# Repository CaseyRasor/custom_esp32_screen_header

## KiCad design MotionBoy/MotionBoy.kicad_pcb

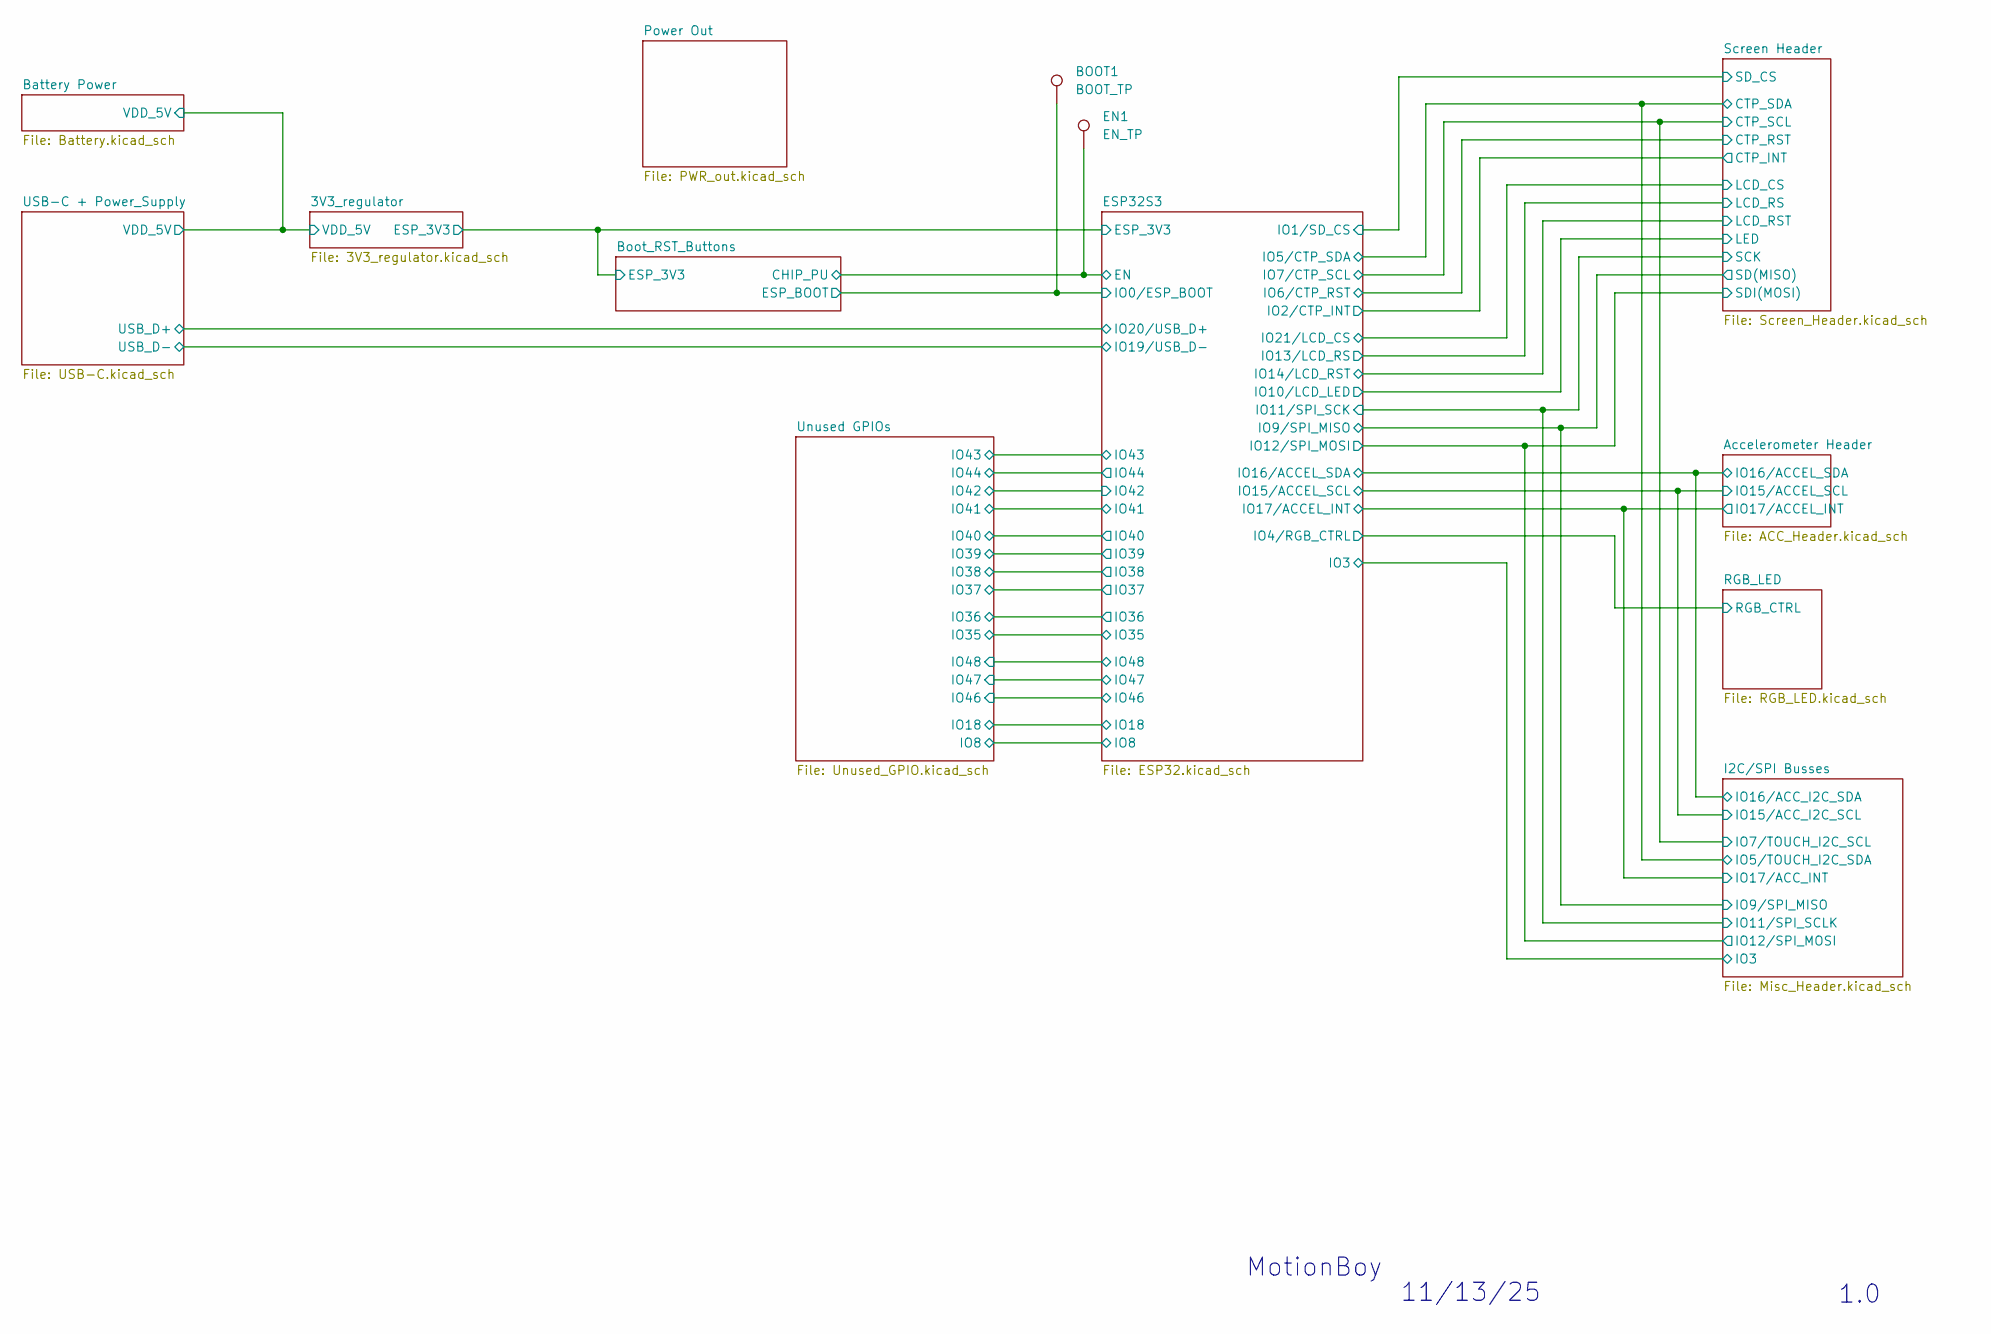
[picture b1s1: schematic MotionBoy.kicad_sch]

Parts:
BOOT1: BOOT_TP; TestPoint_Keystone_5010-5014_Multipurpose
EN1: EN_TP; TestPoint_Keystone_5010-5014_Multipurpose

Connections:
/Boot_RST_Buttons/CHIP_PU: EN1.1; also elsewhere on the board
/Boot_RST_Buttons/ESP_BOOT: BOOT1.1; also elsewhere on the board

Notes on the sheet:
MotionBoy
1.0
11/13/25

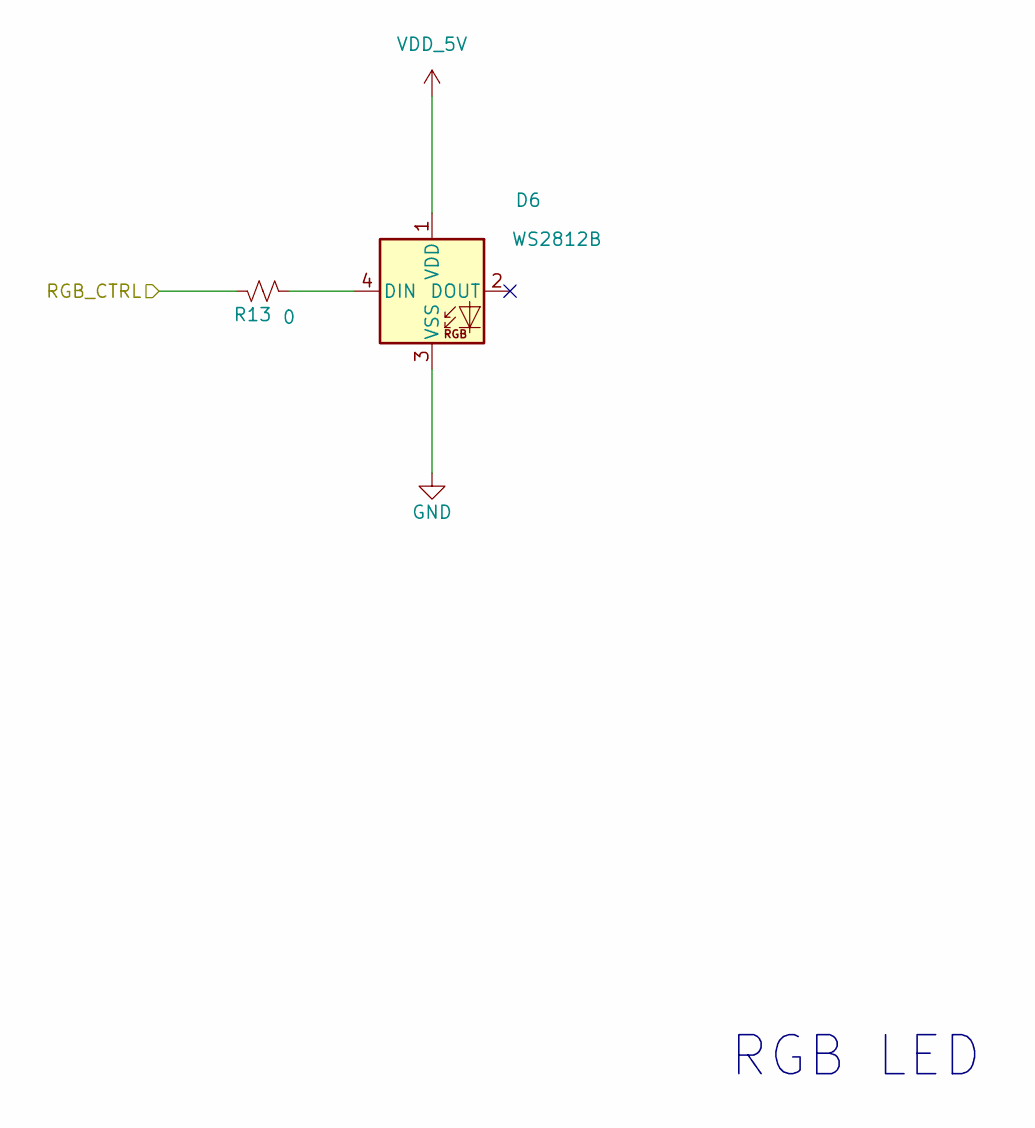
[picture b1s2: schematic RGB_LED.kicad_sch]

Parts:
D6: WS2812B; LED_WS2812B_PLCC4_5.0x5.0mm_P3.2mm
R13: 0; R_0805_2012Metric

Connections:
/ESP32S3/IO4/RGB_CTRL: R13.2; also elsewhere on the board
GND: D6.3 (VSS); also elsewhere on the board
unnamed: D6.4 (DIN), R13.1
VDD_5V: D6.1 (VDD); also elsewhere on the board

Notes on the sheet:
RGB LED

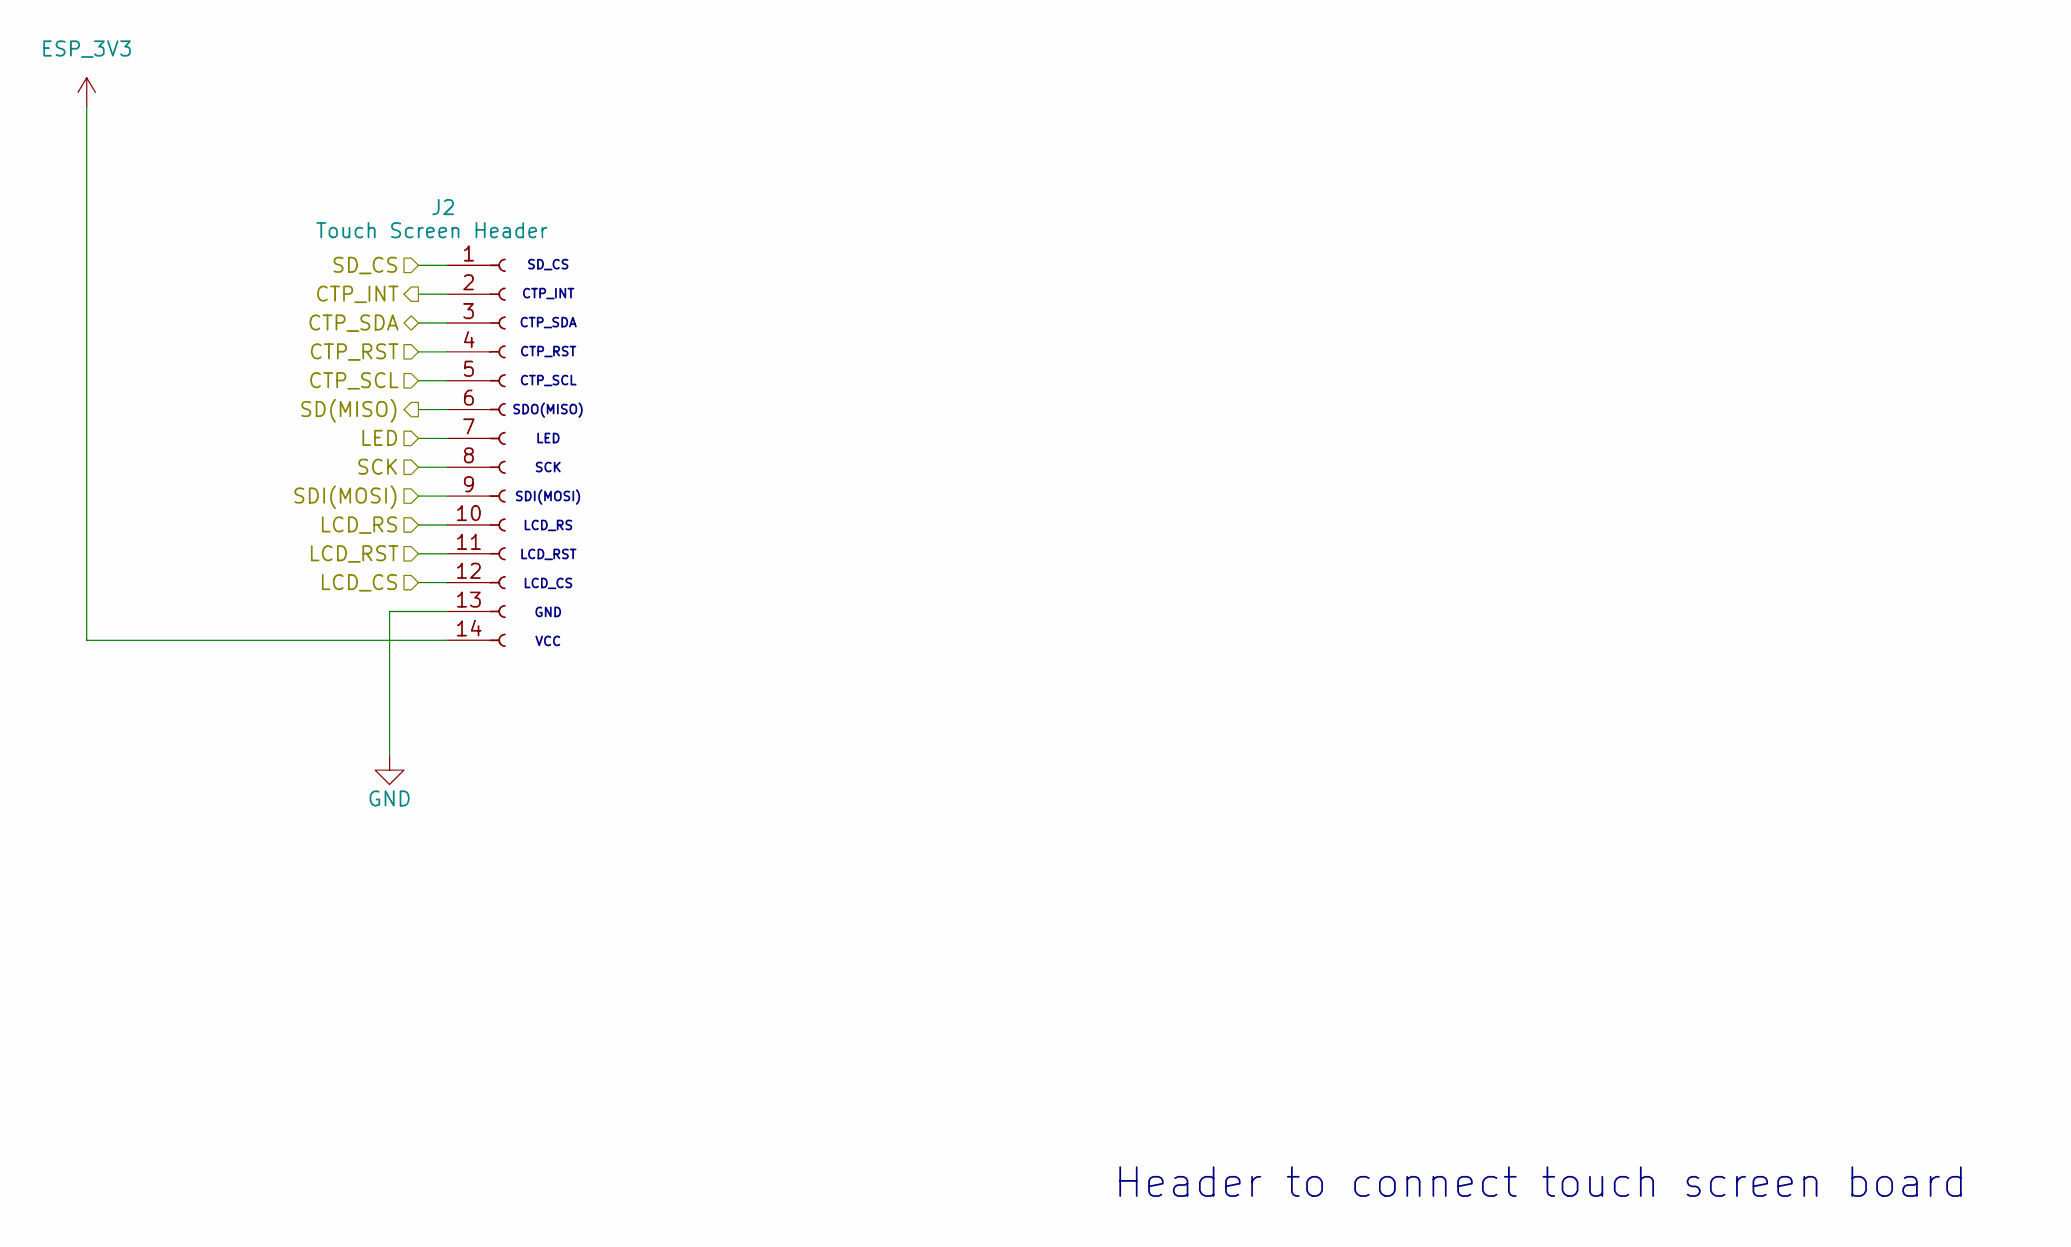
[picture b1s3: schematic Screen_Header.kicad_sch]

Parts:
J2: Touch Screen Header; PinSocket_1x14_P2.54mm_Vertical

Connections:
/ESP32S3/IO1/SD_CS: J2.1; also elsewhere on the board
/ESP32S3/IO2/CTP_INT: J2.2; also elsewhere on the board
/ESP32S3/IO5/CTP_SDA: J2.3; also elsewhere on the board
/ESP32S3/IO6/CTP_RST: J2.4; also elsewhere on the board
/ESP32S3/IO7/CTP_SCL: J2.5; also elsewhere on the board
/ESP32S3/IO9/SPI_MISO: J2.6; also elsewhere on the board
/ESP32S3/IO10/LCD_LED: J2.7; also elsewhere on the board
/ESP32S3/IO11/SPI_SCK: J2.8; also elsewhere on the board
/ESP32S3/IO12/SPI_MOSI: J2.9; also elsewhere on the board
/ESP32S3/IO13/LCD_RS: J2.10; also elsewhere on the board
/ESP32S3/IO14/LCD_RST: J2.11; also elsewhere on the board
/ESP32S3/IO21/LCD_CS: J2.12; also elsewhere on the board
ESP_3V3: J2.14; also elsewhere on the board
GND: J2.13; also elsewhere on the board

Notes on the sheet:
Header to connect touch screen board
SD_CS CTP_INT CTP_SDA CTP_RST CTP_SCL SDO(MISO) LED SCK SDI(MOSI) LCD_RS LCD_RST LCD_CS GND VCC

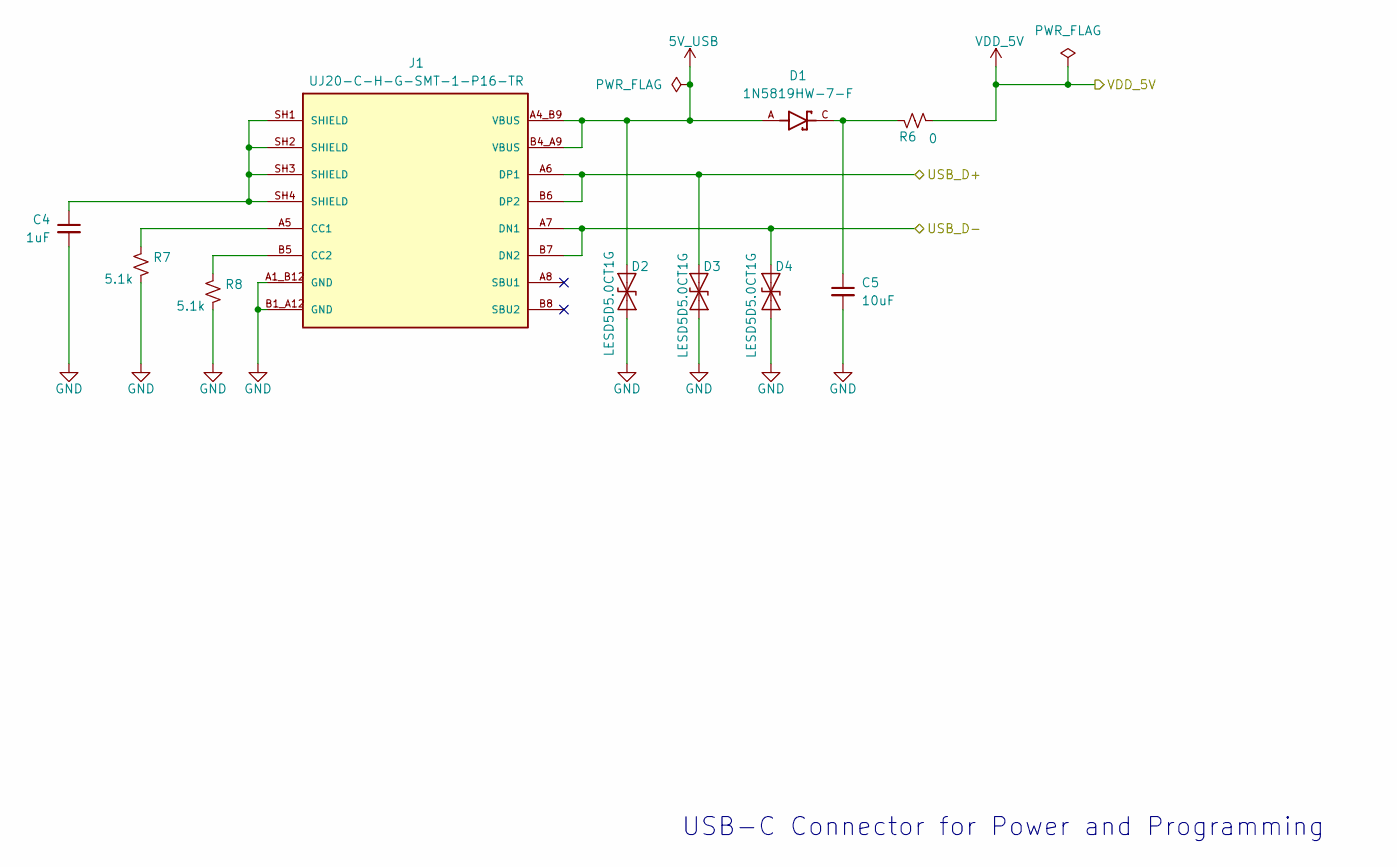
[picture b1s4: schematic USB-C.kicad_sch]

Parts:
C4: 1uF; C_0805_2012Metric
C5: 10uF; C_0805_2012Metric
D1: 1N5819HW-7-F; SOD3715X145N; PARTREV 18-2
D2, D3, D4: LESD5D5.0CT1G; D_SOD-323
J1: UJ20-C-H-G-SMT-1-P16-TR; SAMESKY_UJ20-C-H-G-SMT-1-P16-TR; PARTREV 1.0
R6: 0; R_0805_2012Metric
R7, R8: 5.1k; R_0805_2012Metric

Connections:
5V_USB: D1.A, D2.2 (A2), J1.A4_B9 (VBUS), J1.B4_A9 (VBUS); also elsewhere on the board
/ESP32S3/IO19/USB_D-: D4.2 (A2), J1.A7 (DN1), J1.B7 (DN2); also elsewhere on the board
/ESP32S3/IO20/USB_D+: D3.2 (A2), J1.A6 (DP1), J1.B6 (DP2); also elsewhere on the board
GND: C4.2, C5.2, D2.1 (A1), D3.1 (A1), D4.1 (A1), J1.A1_B12 (GND), J1.B1_A12 (GND), R7.2, R8.2; also elsewhere on the board
unnamed: C4.1, J1.SH1 (SHIELD), J1.SH2 (SHIELD), J1.SH3 (SHIELD), J1.SH4 (SHIELD)
unnamed: C5.1, D1.C, R6.2
unnamed: J1.A5 (CC1), R7.1
unnamed: J1.B5 (CC2), R8.1
VDD_5V: R6.1; also elsewhere on the board

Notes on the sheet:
USB-C Connector for Power and Programming

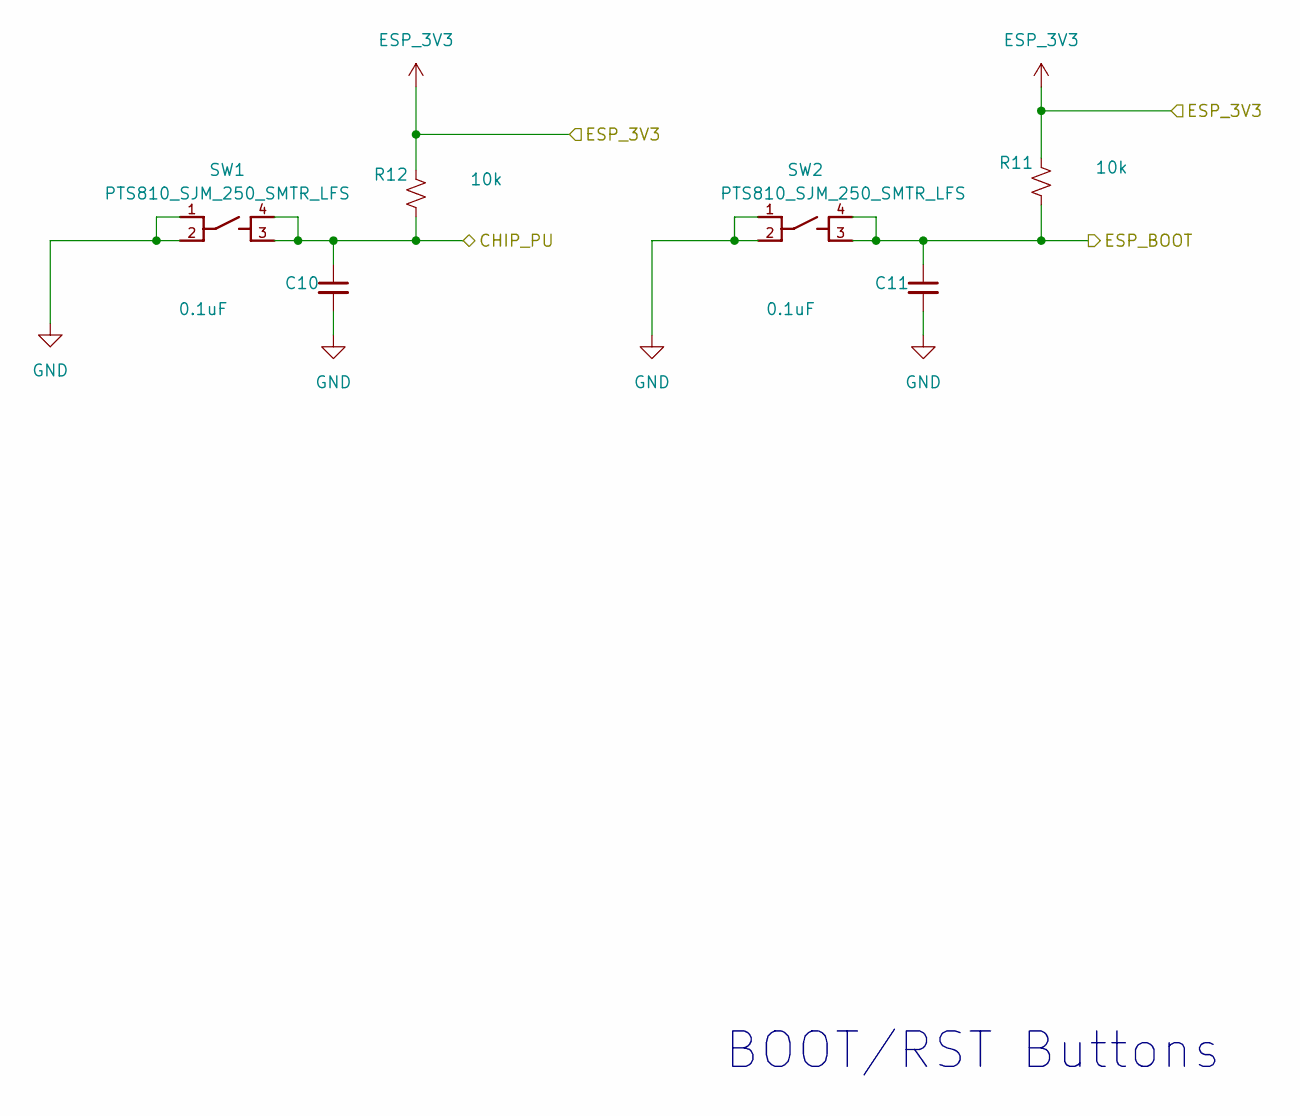
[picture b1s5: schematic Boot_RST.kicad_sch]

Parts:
C10, C11: 0.1uF; C_0805_2012Metric
R11, R12: 10k; R_0805_2012Metric
SW1, SW2: PTS810_SJM_250_SMTR_LFS; SW_PTS810_SJM_250_SMTR_LFS

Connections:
/Boot_RST_Buttons/CHIP_PU: C10.1, R12.1, SW1.3, SW1.4; also elsewhere on the board
/Boot_RST_Buttons/ESP_BOOT: C11.1, R11.1, SW2.3, SW2.4; also elsewhere on the board
ESP_3V3: R11.2, R12.2; also elsewhere on the board
GND: C10.2, C11.2, SW1.1, SW1.2, SW2.1, SW2.2; also elsewhere on the board

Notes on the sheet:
BOOT/RST Buttons

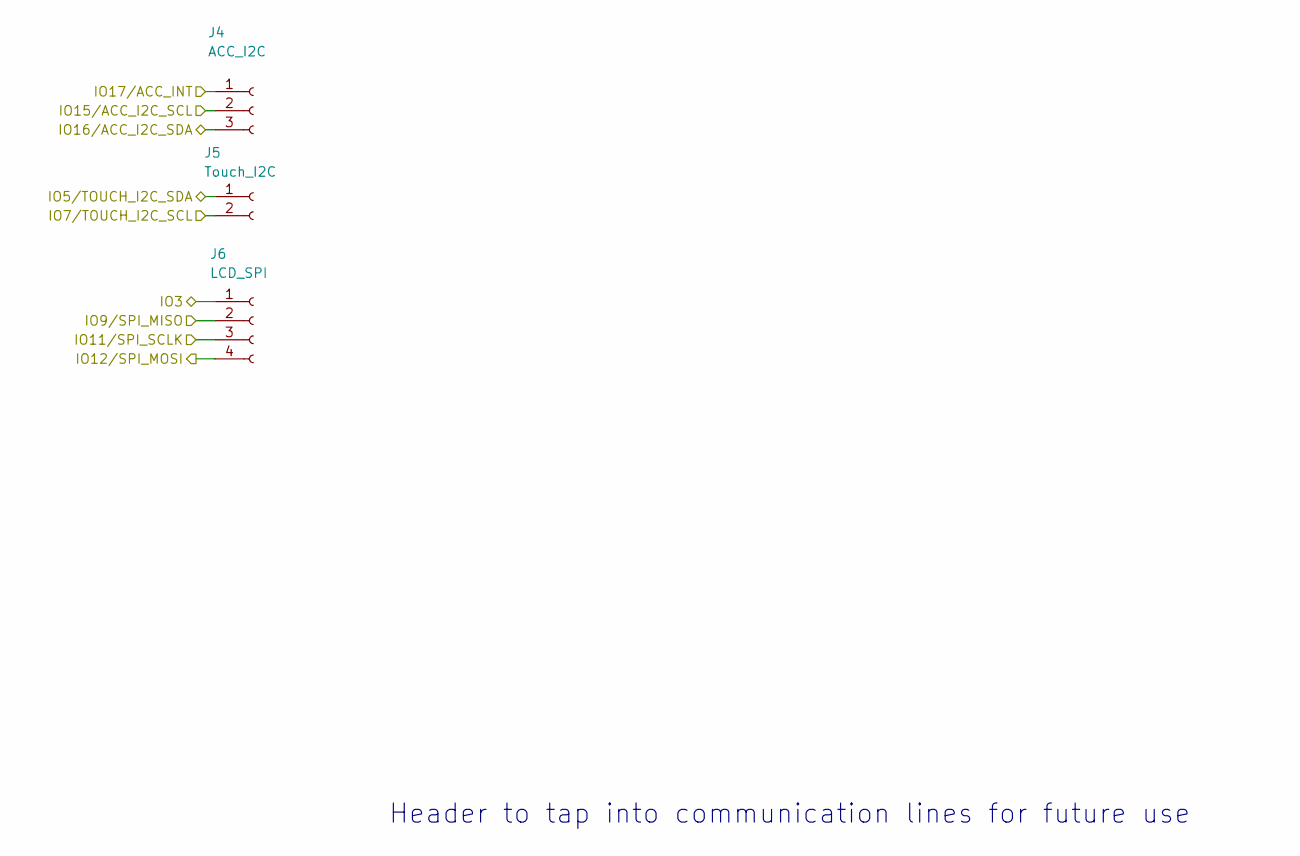
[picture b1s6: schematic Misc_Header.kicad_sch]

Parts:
J4: ACC_I2C; JST_PH_S3B-PH-K_1x03_P2.00mm_Horizontal
J5: Touch_I2C; JST_PH_S2B-PH-K_1x02_P2.00mm_Horizontal
J6: LCD_SPI; JST_PH_S4B-PH-K_1x04_P2.00mm_Horizontal

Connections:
/Accelerometer Header/IO15/ACCEL_SCL: J4.2; also elsewhere on the board
/Accelerometer Header/IO16/ACCEL_SDA: J4.3; also elsewhere on the board
/Accelerometer Header/IO17/ACCEL_INT: J4.1; also elsewhere on the board
/ESP32S3/IO3: J6.1; also elsewhere on the board
/ESP32S3/IO5/CTP_SDA: J5.1; also elsewhere on the board
/ESP32S3/IO7/CTP_SCL: J5.2; also elsewhere on the board
/ESP32S3/IO9/SPI_MISO: J6.2; also elsewhere on the board
/ESP32S3/IO11/SPI_SCK: J6.3; also elsewhere on the board
/ESP32S3/IO12/SPI_MOSI: J6.4; also elsewhere on the board

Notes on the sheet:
Header to tap into communication lines for future use

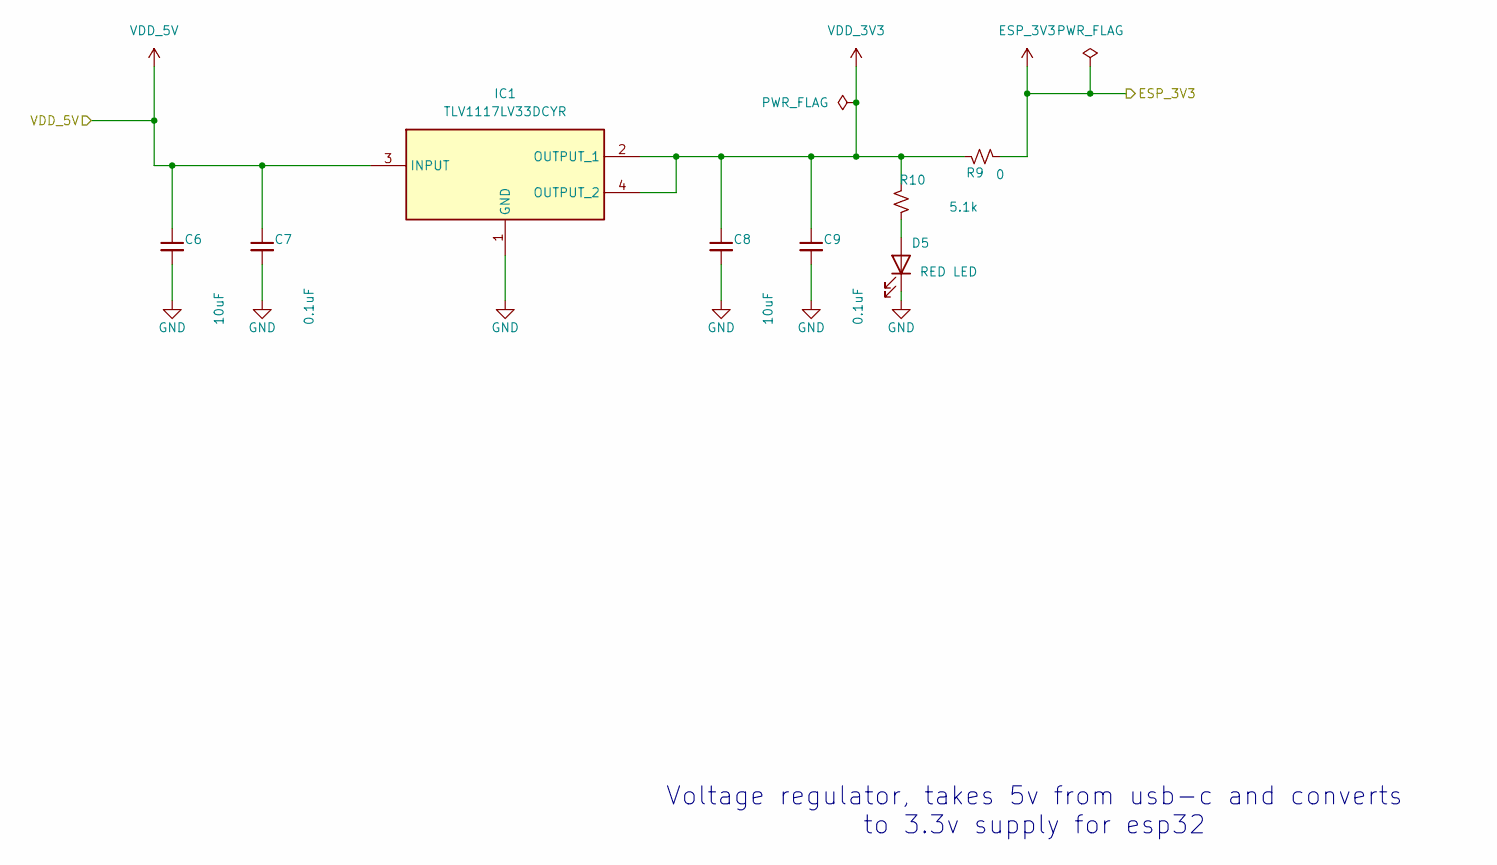
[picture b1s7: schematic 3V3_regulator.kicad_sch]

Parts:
C6, C8: 10uF; C_0805_2012Metric
C7, C9: 0.1uF; C_0805_2012Metric
D5: RED LED; LED_0805_2012Metric
IC1: TLV1117LV33DCYR; SOT230P700X180-4N; Mouser Part Number 595-TLV1117LV33DCYR
R9: 0; R_0805_2012Metric
R10: 5.1k; R_0805_2012Metric

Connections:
ESP_3V3: R9.1; also elsewhere on the board
GND: C6.2, C7.2, C8.2, C9.2, D5.1 (K), IC1.1 (GND); also elsewhere on the board
unnamed: D5.2 (A), R10.2
VDD_3V3: C8.1, C9.1, IC1.2 (OUTPUT_1), IC1.4 (OUTPUT_2), R9.2, R10.1; also elsewhere on the board
VDD_5V: C6.1, C7.1, IC1.3 (INPUT); also elsewhere on the board

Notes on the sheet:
Voltage regulator, takes 5v from usb-c and converts to 3.3v supply for esp32

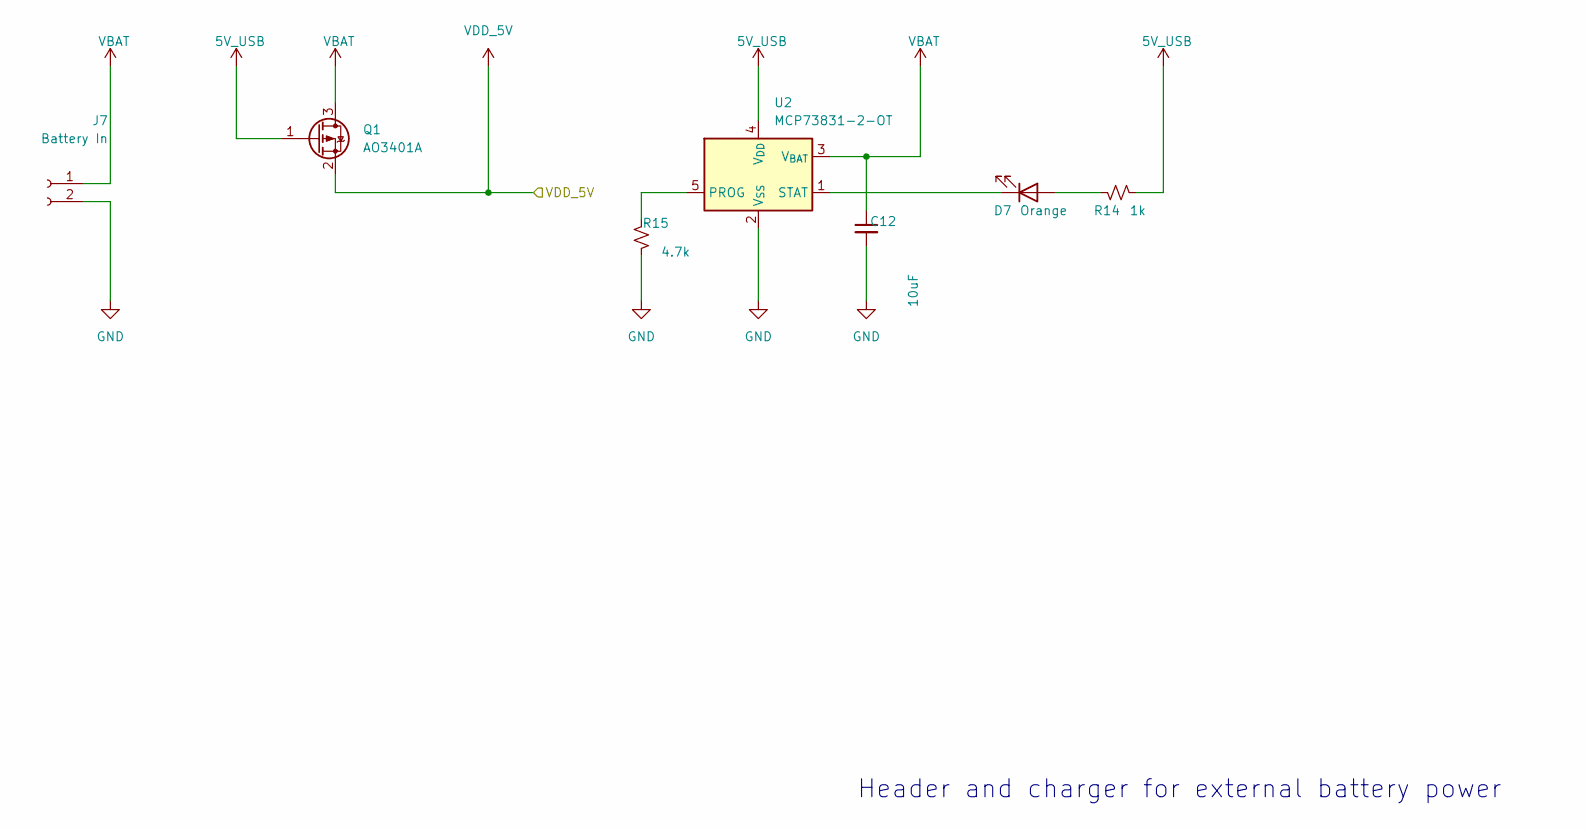
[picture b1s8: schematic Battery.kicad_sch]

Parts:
C12: 10uF; C_0805_2012Metric
D7: Orange; LED_0805_2012Metric
J7: Battery In; JST_PH_S2B-PH-K_1x02_P2.00mm_Horizontal
Q1: AO3401A; SOT-23
R14: 1k; R_0805_2012Metric
R15: 4.7k; R_0805_2012Metric
U2: MCP73831-2-OT; SOT-23-5

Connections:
5V_USB: Q1.1 (G), R14.1, U2.4 (V_{DD}); also elsewhere on the board
GND: C12.2, J7.2, R15.2, U2.2 (V_{SS}); also elsewhere on the board
unnamed: D7.2 (A), R14.2
unnamed: D7.1 (K), U2.1 (STAT)
unnamed: R15.1, U2.5 (PROG)
VBAT: C12.1, J7.1, Q1.3 (D), U2.3 (V_{BAT})
VDD_5V: Q1.2 (S); also elsewhere on the board

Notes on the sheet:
Header and charger for external battery power

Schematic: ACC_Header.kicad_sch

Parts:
J3: Accelerometer Header; PinSocket_1x08_P2.54mm_Vertical

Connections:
/Accelerometer Header/IO15/ACCEL_SCL: J3.3; also elsewhere on the board
/Accelerometer Header/IO16/ACCEL_SDA: J3.4; also elsewhere on the board
/Accelerometer Header/IO17/ACCEL_INT: J3.8; also elsewhere on the board
ESP_3V3: J3.1; also elsewhere on the board
GND: J3.2, J3.7; also elsewhere on the board

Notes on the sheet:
Header to connect accelerometer board
VCC GND SCL SDA XDA XCL ADO INT

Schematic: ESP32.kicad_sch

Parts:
C1: 10uF; C_0805_2012Metric
C2, C3: 0.1uF; C_0805_2012Metric
GND1: GND_TP; TestPoint_Keystone_5010-5014_Multipurpose
R1, R2, R3, R4: 4.7k; R_0805_2012Metric
R5: 10k; R_0805_2012Metric
U1: ESP32-S3-WROOM-1; ESP32S3WROOM1N16R8; PARTREV 1.0; Mouser Part Number 356-ESP32S3WRM1N16R8

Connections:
/Accelerometer Header/IO15/ACCEL_SCL: R3.1, U1.8 (IO15); also elsewhere on the board
/Accelerometer Header/IO16/ACCEL_SDA: R4.1, U1.9 (IO16); also elsewhere on the board
/Accelerometer Header/IO17/ACCEL_INT: U1.10 (IO17); also elsewhere on the board
/Boot_RST_Buttons/CHIP_PU: C3.2, R5.1, U1.3 (EN); also elsewhere on the board
/Boot_RST_Buttons/ESP_BOOT: U1.27 (IO0); also elsewhere on the board
/ESP32S3/IO1/SD_CS: U1.39 (IO1); also elsewhere on the board
/ESP32S3/IO2/CTP_INT: U1.38 (IO2); also elsewhere on the board
/ESP32S3/IO3: U1.15 (IO3); also elsewhere on the board
/ESP32S3/IO4/RGB_CTRL: U1.4 (IO4); also elsewhere on the board
/ESP32S3/IO5/CTP_SDA: R1.1, U1.5 (IO5); also elsewhere on the board
/ESP32S3/IO6/CTP_RST: U1.6 (IO6); also elsewhere on the board
/ESP32S3/IO7/CTP_SCL: R2.1, U1.7 (IO7); also elsewhere on the board
/ESP32S3/IO8: U1.12 (IO8); also elsewhere on the board
/ESP32S3/IO9/SPI_MISO: U1.17 (IO9); also elsewhere on the board
/ESP32S3/IO10/LCD_LED: U1.18 (IO10); also elsewhere on the board
/ESP32S3/IO11/SPI_SCK: U1.19 (IO11); also elsewhere on the board
/ESP32S3/IO12/SPI_MOSI: U1.20 (IO12); also elsewhere on the board
/ESP32S3/IO13/LCD_RS: U1.21 (IO13); also elsewhere on the board
/ESP32S3/IO14/LCD_RST: U1.22 (IO14); also elsewhere on the board
/ESP32S3/IO18: U1.11 (IO18); also elsewhere on the board
/ESP32S3/IO19/USB_D-: U1.13 (IO19); also elsewhere on the board
/ESP32S3/IO20/USB_D+: U1.14 (IO20); also elsewhere on the board
/ESP32S3/IO21/LCD_CS: U1.23 (IO21); also elsewhere on the board
/ESP32S3/IO35: U1.28 (IO35); also elsewhere on the board
/ESP32S3/IO36: U1.29 (IO36); also elsewhere on the board
/ESP32S3/IO37: U1.30 (IO37); also elsewhere on the board
/ESP32S3/IO38: U1.31 (IO38); also elsewhere on the board
/ESP32S3/IO39: U1.32 (IO39); also elsewhere on the board
/ESP32S3/IO40: U1.33 (IO40); also elsewhere on the board
/ESP32S3/IO41: U1.34 (IO41); also elsewhere on the board
/ESP32S3/IO42: U1.35 (IO42); also elsewhere on the board
/ESP32S3/IO43: U1.37 (TXD0); also elsewhere on the board
/ESP32S3/IO44: U1.36 (RXD0); also elsewhere on the board
/ESP32S3/IO46: U1.16 (IO46); also elsewhere on the board
/ESP32S3/IO47: U1.24 (IO47); also elsewhere on the board
/ESP32S3/IO48: U1.25 (IO48); also elsewhere on the board
ESP_3V3: C1.1, C2.1, R1.2, R2.2, R3.2, R4.2, R5.2, U1.2 (3V3); also elsewhere on the board
GND: C1.2, C2.2, C3.1, GND1.1, U1.1 (GND_1), U1.40 (GND_2), U1.41 (GND_3); also elsewhere on the board

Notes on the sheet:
ESP32

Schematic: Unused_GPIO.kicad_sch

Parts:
J8, J9: Unused GPIOs; JST_PH_S4B-PH-K_1x04_P2.00mm_Horizontal
J10, J12: Unused GPIOs; JST_PH_S2B-PH-K_1x02_P2.00mm_Horizontal
J11: Unused GPIOs; JST_PH_S3B-PH-K_1x03_P2.00mm_Horizontal

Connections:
/ESP32S3/IO8: J12.2; also elsewhere on the board
/ESP32S3/IO18: J12.1; also elsewhere on the board
/ESP32S3/IO35: J10.1; also elsewhere on the board
/ESP32S3/IO36: J10.2; also elsewhere on the board
/ESP32S3/IO37: J9.1; also elsewhere on the board
/ESP32S3/IO38: J9.2; also elsewhere on the board
/ESP32S3/IO39: J9.3; also elsewhere on the board
/ESP32S3/IO40: J9.4; also elsewhere on the board
/ESP32S3/IO41: J8.1; also elsewhere on the board
/ESP32S3/IO42: J8.2; also elsewhere on the board
/ESP32S3/IO43: J8.4; also elsewhere on the board
/ESP32S3/IO44: J8.3; also elsewhere on the board
/ESP32S3/IO46: J11.1; also elsewhere on the board
/ESP32S3/IO47: J11.2; also elsewhere on the board
/ESP32S3/IO48: J11.3; also elsewhere on the board

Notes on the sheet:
Header to connect to unused GPIO pins

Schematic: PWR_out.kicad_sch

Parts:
J13, J14: PWR_GND; JST_PH_S3B-PH-K_1x03_P2.00mm_Horizontal

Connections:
GND: J13.3, J14.3; also elsewhere on the board
VDD_3V3: J13.1, J14.1; also elsewhere on the board
VDD_5V: J13.2, J14.2; also elsewhere on the board

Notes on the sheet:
Power out connectors

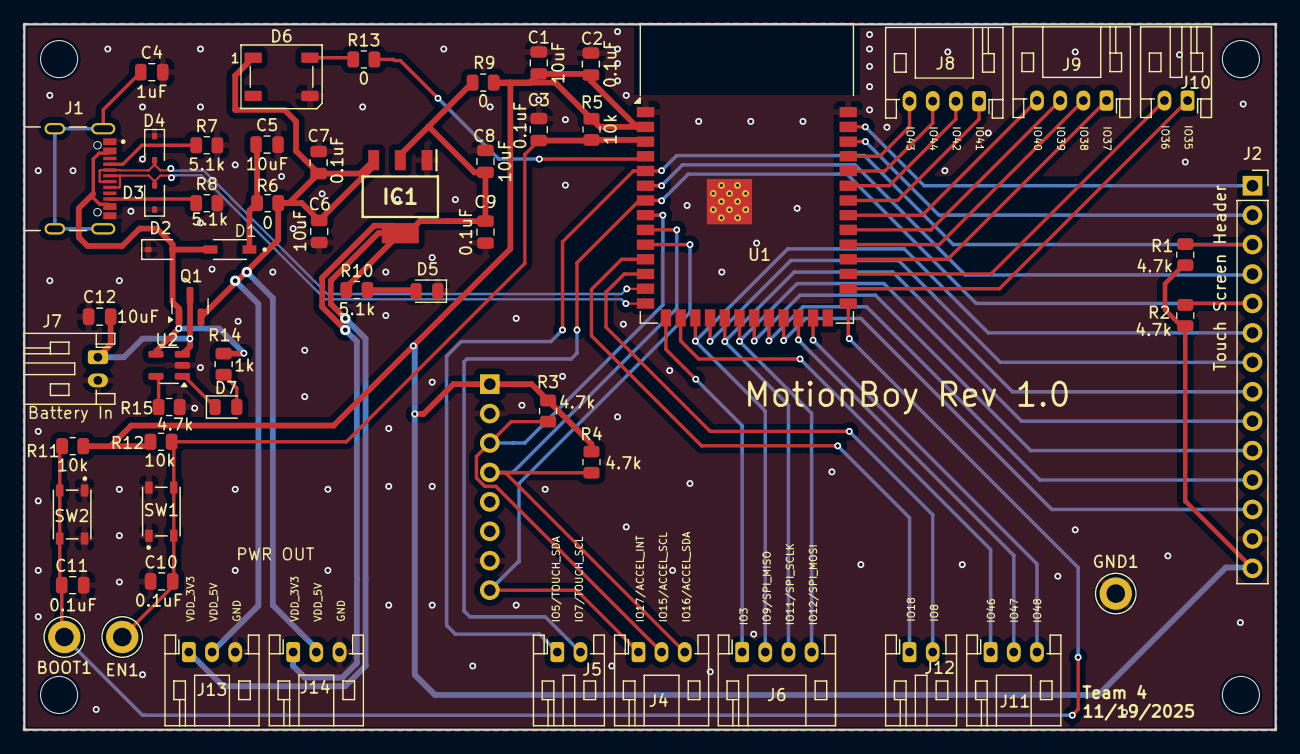
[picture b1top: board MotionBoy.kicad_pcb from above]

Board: 2 copper layers, 108.0 x 60.9 mm, 57 parts (1 on the bottom side), 51 nets.
